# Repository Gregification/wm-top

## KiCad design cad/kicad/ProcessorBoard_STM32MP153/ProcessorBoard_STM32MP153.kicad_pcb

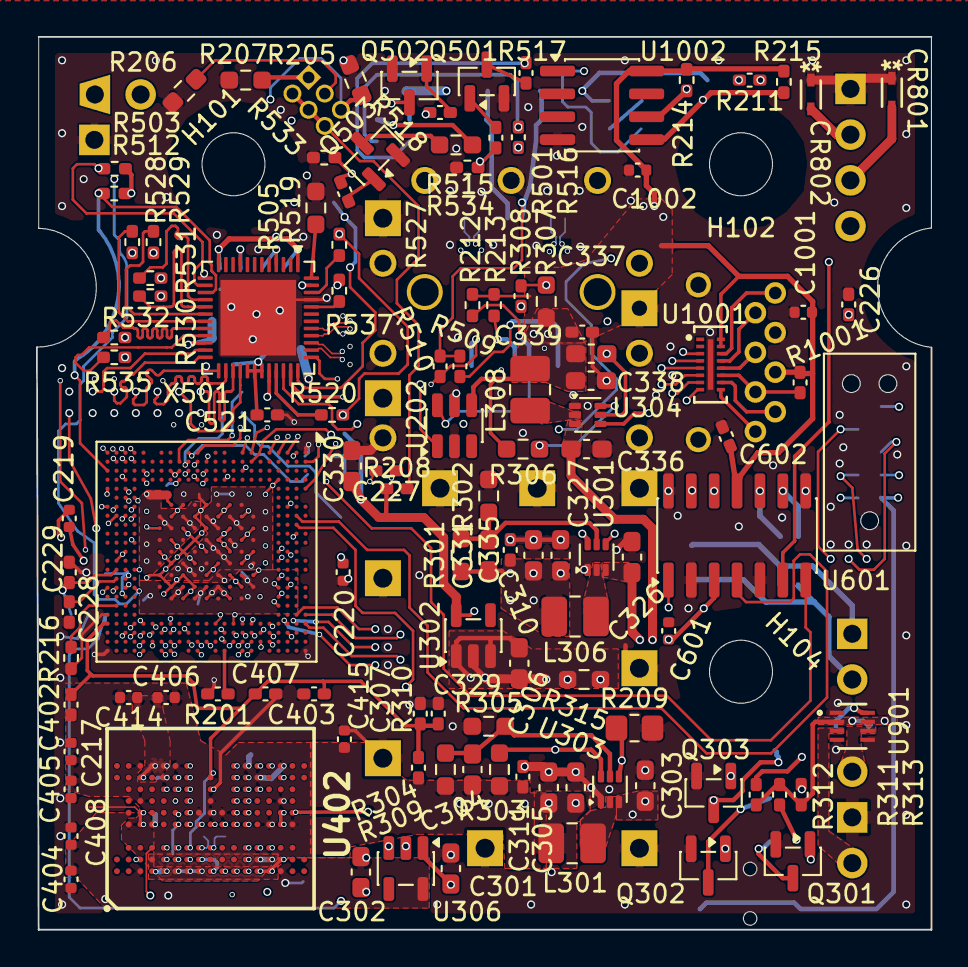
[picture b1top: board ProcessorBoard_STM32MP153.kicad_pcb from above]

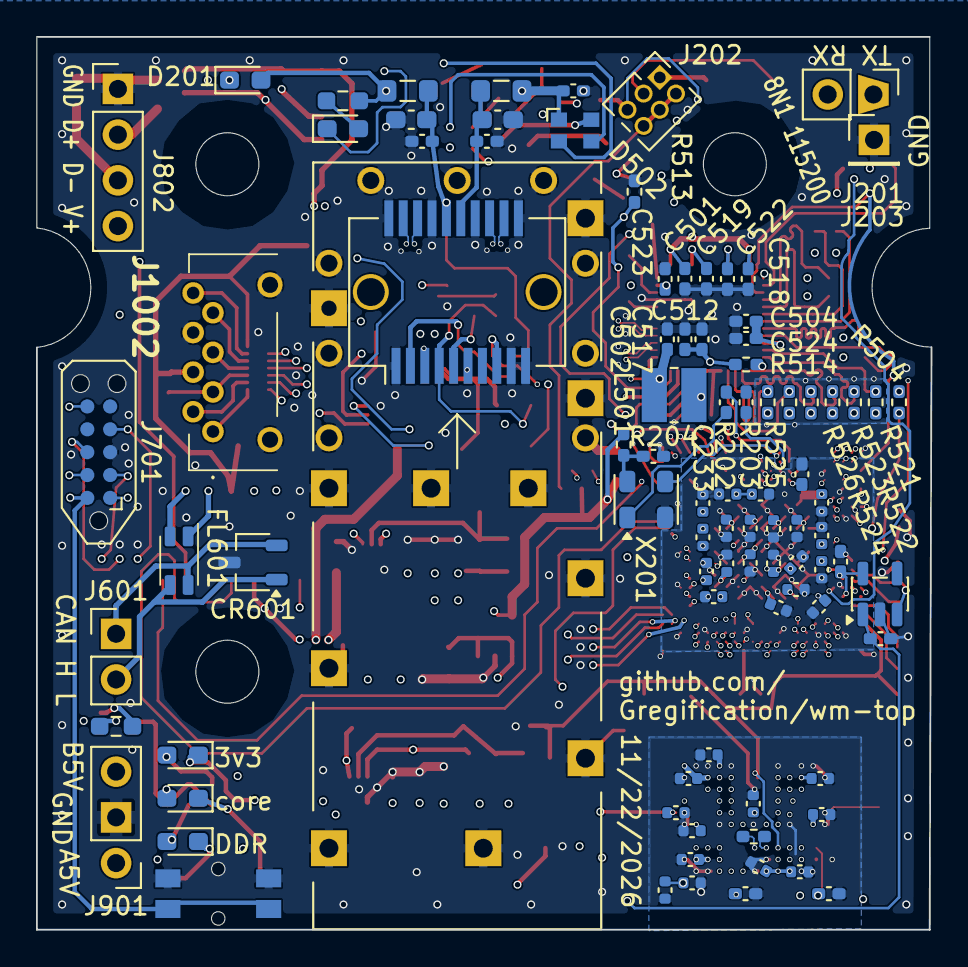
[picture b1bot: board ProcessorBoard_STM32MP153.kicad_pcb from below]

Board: 6 copper layers, 49.7 x 49.6 mm, 208 parts (91 on the bottom side), 177 nets.

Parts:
C201, C202, C204, C205, C206, C208, C209, C210, C211, C212, C213, C214, C215, C216, C217, C218, C219, C220, C221, C222, C223, C401, C404, C405, C406, C412, C418, C419, C420, C421, C422, C601, C1001, C1002: 1u; C_0402_1005Metric
C203, C207, C408, C409, C410, C411, C413, C414, C415, C416: 100n; C_0402_1005Metric
C225, C306, C335, C339, C801, C802: 1u; C_0402_1005Metric_Pad0.74x0.62mm_HandSolder
C226, C233, C307, C501, C506, C507, C510, C518, C519, C521, C522, C523, C524, C602: 100n; C_0402_1005Metric_Pad0.74x0.62mm_HandSolder
C227, C402, C403, C407, C517: 1n; C_0402_1005Metric_Pad0.74x0.62mm_HandSolder
C228, C229, C502, C504, C512: 2.2u; C_0402_1005Metric_Pad0.74x0.62mm_HandSolder
C301, C302, C303, C326, C329, C330, C336, C338, C508, C509: 10u; C_0603_1608Metric_Pad1.08x0.95mm_HandSolder
C304, C331, C337: 22p; C_0603_1608Metric_Pad1.08x0.95mm_HandSolder
C305, C310, C311, C327: 22u; C_0603_1608Metric_Pad1.08x0.95mm_HandSolder
CR601: ESD2CAN36DBZRQ1; TSOT-23
CR801, CR802: ESD321DYAR; SOT5x3_DYA_TEX-M
D201, D503: red; LED_0603_1608Metric_Pad1.05x0.95mm_HandSolder
D301, D302, D303: green; LED_0603_1608Metric_Pad1.05x0.95mm_HandSolder
D502: LED_ABGR; LED_ASMB-KTF0-0A306
FL601: Choke_CommonMode_FerriteCore_1243; L_CommonMode_Wurth_WE-CNSW-1206
H101, H102, H104: MountingHole; MountingHole_3.5mm
J201, J601: Conn_01x02_Pin; PinHeader_1x02_P2.54mm_Vertical
J202: Conn_02x03_Odd_Even; PinHeader_2x03_P1.27mm_Vertical
J203: Conn_01x01_Pin; PinHeader_1x01_P2.54mm_Vertical
J501: SFP; Connector_SFP_and_Cage
J701: TC2050; Tag-Connect_TC2050-IDC-NL_2x05_P1.27mm_Vertical_with_bottom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
J802: Conn_01x04_Pin; PinHeader_1x04_P2.54mm_Vertical
J901: Conn_01x03_Pin; PinHeader_1x03_P2.54mm_Vertical
J1002: PJS008U-3000-0; PJS008U30000
L301, L306, L308: 1u; L_1008_2520Metric_Pad1.43x2.20mm_HandSolder
L501: 2.2u; L_Ferrocore_DLG-0302
L502, L503: 1u; L_0805_2012Metric_Pad1.05x1.20mm_HandSolder
NT301: NetTie_2; NetTie-2_SMD_Pad0.5mm
Q301, Q302, Q303, Q501, Q502, Q503: MMBT5551L; SOT-23
R201, R404, R516, R517: 240; C_0402_1005Metric_Pad0.74x0.62mm_HandSolder
R202, R308, R401, R501, R509, R510, R518, R519, R1001: 10k; C_0402_1005Metric_Pad0.74x0.62mm_HandSolder
R203, R208, R211, R309, R310, R311, R312, R313: 1k; C_0402_1005Metric_Pad0.74x0.62mm_HandSolder
R204: 10; R_0402_1005Metric_Pad0.72x0.64mm_HandSolder
R205, R206, R207, R301, R302, R303, R304, R305, R306, R307, R315, R901: 45.3k; R_0603_1608Metric_Pad0.98x0.95mm_HandSolder
R209: 1M; R_0805_2012Metric_Pad1.20x1.40mm_HandSolder
R212, R213, R214, R215, R216, R503, R512, R513, R514, R533, R534: 3k; R_0402_1005Metric_Pad0.72x0.64mm_HandSolder
R406: 100; R_0402_1005Metric_Pad0.72x0.64mm_HandSolder
R504, R521, R522, R523, R524, R525, R526, R527, R528, R529, R530, R531, R532, R535, R537: 22; R_0402_1005Metric_Pad0.72x0.64mm_HandSolder
R505: 2.49k; R_0603_1608Metric_Pad0.98x0.95mm_HandSolder
R511, R515: 330; R_0603_1608Metric_Pad0.98x0.95mm_HandSolder
R520: 0; R_0402_1005Metric_Pad0.72x0.64mm_HandSolder
SW201: SW_Push; wurth elektronik 4.7x3.5mm side push button
U201: STM32MP153CACx; ST_TFBGA-361_12x12mm_Layout23x23_P0.5mmP0.65mm
U202: TMP101; SOT-23-6
U301, U303, U304: SOT-563
U302, U801: TLV77333; SOT-23-5
U306: TLV77318; SOT-23-5
U402: W97AH6NBVAxx; BGA134C65P10X17_1000X1150X110
U601: TJA1448A; SO-14_3.9x8.65mm_P1.27mm
U901: LM66200DRLR; SOT-5X3_DRL_TEX-M
U1001: EMIF06-MSD02N16; ST MICRO QFN 3.5x1.2 16L 17
U1002: FM24CL16B; SOIC-8_3.9x4.9mm_P1.27mm
X201: ECS-3225MVQ-240-CN-TR; CDFN-4_2.5x3.2mm_P2.1mm
X501: RTL8211FS(I)-xx-xx; QFN-48-1EP_6x6mm_P0.4mm_EP4.2x4.2mm

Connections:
/CAN1.rx: U201.B8 (FDCAN1_RX), U601.4 (RXD1)
/CAN1.tx: U201.B9 (FDCAN1_TX), U601.1 (TXD1)
/CAN2.rx: U201.AC5 (FDCAN2_RX), U601.7 (RXD2)
/CAN2.tx: U201.Y14 (FDCAN2_TX), U601.6 (TXD2)
/I2C_2.SCL: R214.2, U201.A5 (I2C2_SCL), U1002.6 (SCL)
/I2C_2.SDA: R215.2, U201.A2 (I2C2_SDA), U1002.5 (SDA)
/I2C_4.SCL: J501.5 (MOD_DEF1), R213.2, U201.G2 (I2C4_SCL), U202.1 (SCL)
/I2C_4.SDA: J501.4 (MOD_DEF2), R212.2, U201.B10 (I2C4_SDA), U202.6 (SDA)
/IBC/5V_{src1}: J901.1, U901.3 (VIN1)
/IBC/5V_{src2}: J901.3, U901.6 (VIN2)
/PWR_ON: R202.1, R209.1, U201.R2 (PWR_ON), U301.4 (EN), U303.4 (EN), U304.4 (EN), U306.3 (EN)
/SDMCC1.CK: U201.D13 (SDMMC1_CK), U1001.5 (CMD_In)
/SDMCC1.CMD: U201.D12 (SDMMC1_CMD), U1001.6 (CLK_In)
/SDMCC1.D0: U201.D18 (SDMMC1_D0), U1001.4 (DAT3_In)
/SDMCC1.D1: U201.D17 (SDMMC1_D1), U1001.3 (DAT2_In)
/SDMCC1.D2: U201.D15 (SDMMC1_D2), U1001.8 (DAT1_In)
/SDMCC1.D3: U201.D16 (SDMMC1_D3), U1001.7 (DAT0_In)
/SFP/LED_{0}: R519.1, R533.1, X501.35 (PHYAD_{0})
/SFP/LED_{1}: R513.1, R518.1, X501.36 (CFG_LDO_{0})
/SFP/LED_{2}: R501.1, R534.1, X501.37 (CFG_LDO_{1})
/SFP/SERDES_I_N: J501.12 (RD-), X501.39 (HS_I_N)
/SFP/SERDES_I_P: J501.13 (RD+), X501.38 (HS_I_P)
/SFP/SERDES_O_N: J501.19 (TD-), X501.41 (HS_O_N)
/SFP/SERDES_O_P: J501.18 (TD+), X501.40 (HS_O_P)
/SFP/V_{ccR}: C506.1, C508.1, J501.15 (VccR), L502.2
/SFP/V_{ccT}: C507.1, C509.1, J501.16 (VccT), L503.2, R509.1, R510.1
/SFP/ir_1v0: C502.1, C504.1, C519.2, C522.2, C523.2, C524.2, L501.2, X501.4 (AV_{dd}1v0), X501.9 (AV_{dd}1v0), X501.22 (DV_{dd}1v0), X501.47 (AV_{dd}1v0)
/SFP/ir_out: L501.1, X501.32 (REG_OUT)
/SOC/Boot0: J202.1, R207.2, U201.N1 (BOOT0)
/SOC/Boot1: J202.3, R206.2, U201.N4 (BOOT1)
/SOC/Boot2: J202.5, R205.2, U201.M2 (BOOT2)
/SOC/OSC_HSE_in: U201.P1 (RCC_OSC_IN), X201.3 (OUT)
/SOC/OSC_HSE_out: R203.1, U201.P2 (RCC_OSC_OUT)
/SOC/UART_{4}_RX: J201.2, U201.Y16 (UART4_RX)
/SOC/UART_{4}_TX: J201.1, U201.Y7 (ETH1_TX_CTL)
/SOC/boot fail led: R211.1, U201.N2 (PA13)
/USB_2.D+: CR802.2 (I/O), J802.2, U201.AC16 (USB_DP2)
/USB_2.D-: CR801.2 (I/O), J802.3, U201.AB16 (USB_DM2)
/V_{DDR_ref}: C307.1, C402.1, C403.1, C407.1, R309.2, R310.1, U201.AC20 (DDR_VREF), U402.G3 (VREF(CA)), U402.J9 (VREF(DQ))
/V_{ddA_ADC}: NT301.2, U201.1H1 (VDDA)
/V_{ddA}_1v8: C229.2, U201.AB14 (VDDA1V8_REG), U801.3 (EN)
/V_{dd_DDR1}_1v8: C302.1, C401.2, C404.2, C408.1, C409.1, C410.1, U306.5 (OUT), U402.B6 (VDD1), U402.C1 (VDD1), U402.R1 (VDD1), U402.T6 (VDD1)
/V_{dd_DDRQ}_1v2: C203.1, C204.2, C207.1, C208.2, C211.2, C214.2, C217.2, C304.1, C305.1, C306.1, C311.1, C405.2, C406.2, C411.1, C412.2, C413.1, C414.1, C415.1, C416.1, C418.2, C419.2, C420.2, C421.2, C422.2, L301.1, R303.2, R304.1, R309.1, U201.1A8 (VDDQ_DDR), U201.1B7 (VDDQ_DDR), U201.1B9 (VDDQ_DDR), U201.1C8 (VDDQ_DDR), U201.1D9 (VDDQ_DDR), U201.1E8 (VDDQ_DDR), U201.1F9 (VDDQ_DDR), U201.1G8 (VDDQ_DDR), U201.1H9 (VDDQ_DDR), U201.1J8 (VDDQ_DDR), U402.B5 (VDD2), U402.C7 (VDDQ), U402.C10 (VDDQ), U402.D2 (VDD2), U402.D5 (VDDQ), U402.E9 (VDDQ), U402.F1 (VDDCA), U402.F10 (VDDQ), U402.G1 (VDD2), U402.H1 (VDDCA), U402.H6 (VDDQ), U402.J6 (VDDQ), U402.J7 (VDD2), U402.K6 (VDDQ), U402.M10 (VDDQ), U402.N2 (VDDCA), U402.N9 (VDDQ), U402.P2 (VDD2), U402.P5 (VDDQ), U402.R7 (VDDQ), U402.R10 (VDDQ), U402.T5 (VDD2)
/V_{dd_USB}_3v3: C801.1, U201.AA15 (VDD3V3_USBHS), U201.AA17 (VDD3V3_USBFS), U801.5 (OUT)
/V_{dd_board}_3v3: C337.1, C338.1, C339.1, C501.2, C510.1, C512.2, C517.2, C518.2, C521.2, C602.1, C1001.2, C1002.2, D201.2 (A), D502.1 (A), J1002.4 (Vdd), L308.1, L502.1, L503.1, R212.1, R213.1, R214.1, R215.1, R306.2, R307.1, R503.1, R511.2, R512.1, R514.1, R1001.2, U202.4 (V+), U601.11 (VIO), U1001.15 (Vcc), U1001.16 (DAT3_pull_-up), U1002.8 (VDD), X501.1 (AV_{dd}3v3), X501.12 (AV_{dd}3v3), X501.29 (DV_{dd}_RG), X501.30 (DV_{dd}3v3), X501.31 (V_{dd}_REG)
/V_{dd_core}_1v2: C201.2, C205.2, C209.2, C212.2, C215.2, C218.2, C220.2, C221.2, C222.2, C223.2, C310.1, C327.1, C331.1, C335.1, L306.1, R301.1, R315.2, U201.1A2 (VDDCORE), U201.1A4 (VDDCORE), U201.1A6 (VDDCORE), U201.1B1 (VDDCORE), U201.1B3 (VDDCORE), U201.1B5 (VDDCORE), U201.1C2 (VDDCORE), U201.1C4 (VDDCORE), U201.1C6 (VDDCORE), U201.1D1 (VDDCORE), U201.1D3 (VDDCORE), U201.1D5 (VDDCORE), U201.1D7 (VDDCORE), U201.1E2 (VDDCORE), U201.1E4 (VDDCORE), U201.1E6 (VDDCORE), U201.1F5 (VDDCORE), U201.1F7 (VDDCORE), U201.1G6 (VDDCORE), U201.1H7 (VDDCORE)
/ddr.CKE: R401.1, U201.T20 (DDR_CKE), U402.K1 (CKE0)
/ddr.CLK_N: R406.2, U201.N23 (DDR_CLKN), U402.H3 (CK_c)
/ddr.CLK_P: R406.1, U201.N22 (DDR_CLKP), U402.J3 (CK_t)
/ddr.CSn: U201.M22 (DDR_CSN), U402.L1 (CS0_n)
/ddr.a0: U201.L20 (DDR_A0), U402.P3 (CA0)
/ddr.a1: U201.P22 (DDR_A1), U402.N3 (CA1)
/ddr.a2: U201.J20 (DDR_A2), U402.M3 (CA2)
/ddr.a3: U201.K22 (DDR_A3), U402.M2 (CA3)
/ddr.a4: U201.V20 (DDR_A4), U402.M1 (CA4)
/ddr.a5: U201.H20 (DDR_A5), U402.G2 (CA5)
/ddr.a6: U201.W20 (DDR_A6), U402.F2 (CA6)
/ddr.a7: U201.E20 (DDR_A7), U402.F3 (CA7)
/ddr.a8: U201.Y20 (DDR_A8), U402.E3 (CA8)
/ddr.a9: U201.G20 (DDR_A9), U402.E2 (CA9)
/ddr.d0: U201.E22 (DDR_DQ0), U402.N8 (DQ0)
/ddr.d1: U201.F22 (DDR_DQ1), U402.M8 (DQ1)
/ddr.d2: U201.H21 (DDR_DQ2), U402.M7 (DQ2)
/ddr.d3: U201.E21 (DDR_DQ3), U402.M9 (DQ3)
/ddr.d4: U201.J21 (DDR_DQ4), U402.M6 (DQ4)
/ddr.d5: U201.J22 (DDR_DQ5), U402.L7 (DQ5)
/ddr.d6: U201.H22 (DDR_DQ6), U402.L8 (DQ6)
/ddr.d7: U201.G21 (DDR_DQ7), U402.L9 (DQ7)
/ddr.d8: U201.T21 (DDR_DQ8), U402.G7 (DQ10)
/ddr.d9: U201.U21 (DDR_DQ9), U402.G9 (DQ8)
/ddr.d10: U201.T22 (DDR_DQ10), U402.E8 (DQ15)
/ddr.d11: U201.W21 (DDR_DQ11), U402.F8 (DQ14)
/ddr.d12: U201.W23 (DDR_DQ12), U402.F6 (DQ11)
/ddr.d13: U201.T23 (DDR_DQ13), U402.F7 (DQ13)
/ddr.d14: U201.W22 (DDR_DQ14), U402.F9 (DQ12)
/ddr.d15: U201.Y21 (DDR_DQ15), U402.G8 (DQ9)
/ddr.m0: U201.H23 (DDR_DQM0), U402.K5 (DM0)
/ddr.m1: U201.V22 (DDR_DQM1), U402.H5 (DM1)
/ddr.s0_N: U201.G23 (DDR_DQS0N), U402.L5 (DQS0_c)
/ddr.s0_P: U201.G22 (DDR_DQS0P), U402.L6 (DQS0_t)
/ddr.s1_N: U201.U23 (DDR_DQS1N), U402.G5 (DQS1_c)
/ddr.s1_P: U201.U22 (DDR_DQS1P), U402.G6 (DQS1_t)
/jtag_tc2050.TCK: J701.4, U201.B20 (JTCK)
/jtag_tc2050.TDI: J701.8, U201.A20 (JTDI)
/jtag_tc2050.TDO: J701.6, U201.A19 (JTDO)
/jtag_tc2050.TMS: J701.2, U201.C20 (JTMS)
/jtag_tc2050.V_{cc}: C202.2, C206.2, C210.2, C213.2, C216.2, C219.2, C330.1, J701.1, NT301.1, R204.1, R208.1, U201.1F1 (VBAT), U201.1F3 (VDD), U201.1G2 (VDD_ANA), U201.1G4 (VDD), U201.1H3 (VDD), U201.1H5 (VDD), U201.1J2 (VDD), U201.1J4 (VDD), U201.1J6 (VDD), U201.R3 (PDR_ON), U201.T3 (PDR_ON_CORE), U302.5 (OUT)
/jtag_tc2050.nSRST: C226.1, C227.1, J701.10, SW201.2, U201.M3 (NRST)
/jtag_tc2050.nTRST: J701.9, U201.B19 (NJTRST)
/offboard5v: C301.1, C303.1, C326.1, C329.1, C336.1, C601.2, C802.1, R311.1, R312.1, R313.1, R901.1, U301.3 (V_{in}), U302.1 (IN), U302.3 (EN), U303.3 (V_{in}), U304.3 (V_{in}), U306.1 (IN), U601.3 (VCC), U801.1 (IN), U901.2 (VOUT), U901.7 (VOUT)
/sfp.led_{red}: D503.1 (K), U201.E1 (PI3)
/sfp.macphy_clk_25: R520.1, R527.1, U201.Y8 (ETH1_CLK)
/sfp.mdc: R504.1, U201.AA6 (ETH1_MDC)
/sfp.mdio: R512.2, U201.AC3 (ETH1_MDIO), X501.15 (MDIO)
/sfp.module.present: J501.6 (MOD_DEF0), U201.G1 (PZ1)
/sfp.module.rx_loss: J501.8 (RX_LOS), R510.2, U201.C1 (PI0)
/sfp.module.tx_disable: J501.3 (TX_DISABLE), U201.D1 (PH13)
/sfp.module.tx_fault: J501.2 (TX_FAULT), R509.2, U201.B1 (PH15)
/sfp.phy.int#: U201.K4 (ETH1_PHY_INTN), X501.34 (INTB/PMEB)
/sfp.phy.reset#: U201.H1 (PZ6), X501.13 (PHY_RSTB#)
/sfp.phymac_frclk_125: R537.1, U201.Y6 (ETH1_CLK125)
/sfp.rxc: R526.1, U201.AA4 (ETH1_RX_CLK)
/sfp.rxctl: R525.1, U201.AB8 (ETH1_RX_CTL)
/sfp.rxd0: R524.1, U201.AC7 (ETH1_RXD0)
/sfp.rxd1: R523.1, U201.AB7 (ETH1_RXD1)
/sfp.rxd2: R522.1, U201.Y11 (ETH1_RXD2)
/sfp.rxd3: R521.1, U201.W4 (ETH1_RXD3)
/sfp.txc: R535.1, U201.AB2 (ETH1_GTX_CLK)
/sfp.txctl: R532.1, U201.AB1 (PB11)
/sfp.txd0: R528.1, U201.AA2 (ETH1_TXD0)
/sfp.txd1: R529.1, U201.AA1 (ETH1_TXD1)
/sfp.txd2: R530.1, U201.Y2 (ETH1_TXD2)
/sfp.txd3: R531.1, U201.Y1 (ETH1_TXD3)
GND: C201.1, C202.1, C203.2, C204.1, C205.1, C206.1, C207.2, C208.1, C209.1, C210.1, C211.1, C212.1, C213.1, C214.1, C215.1, C216.1, C217.1, C218.1, C219.1, C220.1, C221.1, C222.1, C223.1, C225.1, C226.2, C228.1, C229.1, C233.2, C301.2, C302.2, C303.2, C305.2, C306.2, C307.2, C310.2, C311.2, C326.2, C327.2, C329.2, C330.2, C335.2, C336.2, C338.2, C339.2, C401.1, C402.2, C403.2, C404.1, C405.1, C406.1, C407.2, C408.2, C409.2, C410.2, C411.2, C412.1, C413.2, C414.2, C415.2, C416.2, C418.1, C419.1, C420.1, C421.1, C422.1, C501.1, C502.2, C504.2, C506.2, C507.2, C508.2, C509.2, C510.2, C512.1, C517.1, C518.1, C519.1, C521.1, C522.1, C523.1, C524.1, C601.1, C602.2, C801.2, C802.2, C1001.1, C1002.1, CR601.3, CR801.1 (GND), CR802.1 (GND), J203.1 (Pin_1_1), J501.1 (VeeT), J501.9 (VeeR), J501.10 (VeeR), J501.11 (VeeR), J501.14 (VeeR), J501.17 (VeeT), J501.20 (VeeT), J501.CAGE, J701.3, J802.1, J901.2, J1002.6 (Vss), J1002.MH1, J1002.MH2, Q301.2 (E), Q302.2 (E), Q303.2 (E), Q501.2 (E), Q502.2 (E), Q503.2 (E), R201.2, R203.2, R205.1, R206.1, R207.1, R209.2, R216.1, R302.2, R305.2, R308.2, R310.2, R401.2, R404.2, R505.2, R513.2, R533.2, R534.2, SW201.1, U201.1A3 (VSS), U201.1A5 (VSS), U201.1A7 (VSS), U201.1B2 (VSS), U201.1B4 (VSS), U201.1B6 (VSS), U201.1B8 (VSS), U201.1C1 (VSS), U201.1C3 (VSS), U201.1C5 (VSS), U201.1C7 (VSS), U201.1C9 (VSS), U201.1D2 (VSS), U201.1D4 (VSS), U201.1D6 (VSS), U201.1D8 (VSS), U201.1E1 (VSS), U201.1E3 (VSS), U201.1E5 (VSS), U201.1E7 (VSS), U201.1E9 (VSS), U201.1F2 (VSS), U201.1F4 (VSS), U201.1F6 (VSS), U201.1F8 (VSS), U201.1G1 (VSS_ANA), U201.1G3 (VSS), U201.1G5 (VSS), U201.1G7 (VSS), U201.1G9 (VSS), U201.1H2 (VSSA), U201.1H4 (VSS), U201.1H6 (VSS), U201.1H8 (VSS), U201.1J3 (VSS), U201.1J5 (VSS), U201.1J7 (VSS), U201.A1 (VSS), U201.A23 (VSS), U201.AA5 (VSS), U201.AA8 (VSS), U201.AA12 (VSS), U201.AA16 (VSS_USBHS), U201.AA21 (VSS), U201.AB13 (BYPASS_REG1V8), U201.AC1 (VSS), U201.AC19 (OTG_VBUS), U201.AC23 (VSS), U201.C7 (VSS), U201.C12 (VSS), U201.C16 (VSS), U201.C21 (VSS), U201.D4 (VSS), U201.F21 (VSS), U201.H3 (VSS), U201.K21 (VSS), U201.P3 (VSS), U201.P21 (VSS), U201.V21 (VSS), U201.W3 (VSS), U202.2 (GND), U202.5 (ADD0), U301.1 (GND), U302.2 (GND), U303.1 (GND), U304.1 (GND), U306.2 (GND), U402.C2 (VSS), U402.C5 (VSS), U402.C6 (VSSQ), U402.C9 (VSSQ), U402.D1 (VSS), U402.D10 (VSSQ), U402.E1 (VSS), U402.E10 (VSSQ), U402.F5 (VSSQ), U402.G10 (VSSQ), U402.H2 (VSS), U402.J1 (VSS), U402.J5 (VSSQ), U402.J8 (VSS), U402.L10 (VSSQ), U402.M5 (VSSQ), U402.N1 (VSS), U402.N10 (VSSQ), U402.P1 (VSS), U402.P10 (VSSQ), U402.R2 (VSS), U402.R5 (VSS), U402.R6 (VSSQ), U402.R9 (VSSQ), U601.2 (GND), U601.5 (GND), U601.8 (STB2), U601.14 (STB1), U801.2 (GND), U901.1 (GND), U901.4 (ON#), U901.5 (GND), U1001.17 (GND), U1002.4 (VSS), X201.2 (GND), X501.45 (XTAL_IN), X501.49 (GND)
unnamed: D201.1 (K), R211.2
unnamed: D301.2 (A), R311.2
unnamed: D301.1 (K), Q301.3 (C)
unnamed: D302.2 (A), R313.2
unnamed: D302.1 (K), Q302.3 (C)
unnamed: D303.2 (A), R312.2
unnamed: D303.1 (K), Q303.3 (C)
unnamed: D502.2 (BK), R517.2
unnamed: D502.3 (GK), R516.2
unnamed: D502.4 (RK), R515.2
unnamed: D503.2 (A), R511.1
unnamed: J202.2, J202.4, J202.6, R208.2
unnamed: CR601.2, FL601.2, J601.1
unnamed: CR601.1, FL601.3, J601.2
unnamed: J1002.5 (CLK), U1001.12 (CMD_Ex)
unnamed: J1002.3 (CMD), R1001.1, U1001.11 (CLK_Ex)
unnamed: J1002.7 (DAT0), U1001.13 (DAT3_Ex)
unnamed: J1002.8 (DAT1), U1001.14 (DAT2_Ex)
unnamed: J1002.1 (DAT2), U1001.9 (DAT1_Ex)
unnamed: J1002.2 (DAT3), U1001.10 (DAT0_Ex)
unnamed: Q301.1 (B), R303.1, U303.6 (PG)
unnamed: Q302.1 (B), R315.1, U301.6 (PG)
unnamed: Q303.1 (B), R306.1, U304.6 (PG)
unnamed: Q501.1 (B), R501.2
unnamed: Q501.3 (C), R517.1
unnamed: Q502.1 (B), R518.2
unnamed: Q502.3 (C), R516.1
unnamed: Q503.1 (B), R519.2
unnamed: Q503.3 (C), R515.1
unnamed: R201.1, U201.K23 (DDR_ZQ)
unnamed: C227.2, U201.M4 (NRST_CORE)
unnamed: R216.2, U201.AB18 (USB_RREF)
unnamed: C228.2, U201.AB15 (VDDA1V1_REG)
unnamed: C225.2, U201.R4 (VREF+)
unnamed: C331.2, R301.2, R302.1, U301.5 (FB)
unnamed: L306.2, U301.2 (SW)
unnamed: C304.2, R304.2, R305.1, U303.5 (FB)
unnamed: L301.2, U303.2 (SW)
unnamed: C337.2, R307.2, R308.1, U304.5 (FB)
unnamed: L308.2, U304.2 (SW)
unnamed: R404.1, U402.D3 (ZQ)
unnamed: FL601.1, U601.10 (CANH2), U601.13 (CANH1)
unnamed: FL601.4, U601.9 (CANL2), U601.12 (CANL1)
unnamed: R901.2, U901.8 (ST)
unnamed: R202.2, X201.1 (EN)
unnamed: C233.1, R204.2, X201.4 (V_{dd})
unnamed: R514.2, R523.2, X501.25 (CFG_{mode0})
unnamed: R522.2, X501.24 (CFG_{mode1})
unnamed: R521.2, X501.23 (CFG_{mode2})
unnamed: R537.2, X501.44 (CLKOUT)
unnamed: R503.2, R504.2, X501.14 (MDC)
unnamed: R526.2, X501.28 (PHYAD_{1})
unnamed: R525.2, X501.27 (PHYAD_{2})
unnamed: R520.2, X501.33 (PTP_CLKIN/GPIO_{0})
unnamed: R505.1, X501.48 (RSET)
unnamed: R524.2, X501.26 (RXDLY)
unnamed: R535.2, X501.21 (TXCLK)
unnamed: R532.2, X501.20 (TXCTL)
unnamed: R528.2, X501.19 (TXD_{0})
unnamed: R529.2, X501.18 (TXD_{1})
unnamed: R530.2, X501.17 (TXD_{2})
unnamed: R531.2, X501.16 (TXD_{3})
unnamed: R527.2, X501.46 (XTAL_OUT)
